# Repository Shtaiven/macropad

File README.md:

# QMK Macropad 5x5

A 5x5 key macropad with USB-C connector for Cherry MX-style switches.

## Repo structure

* [ecad](ecad) contains the electrical CAD files (KiCad).
* [mcad](mcad) contains the mechanical CAD files (SolidWorks).

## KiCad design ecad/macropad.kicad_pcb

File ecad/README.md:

# PCB Design

## MCU preferences

* Support both QMK (ChibiOS) and custom ducky firmware.
* MCU must be hand solderable.
* Must have USB stack  on SoC.
* ARM Cortex 32-bit based (M0 or M4).
* Ideally below $15.
* Support mounting as mass storage.
* Support DFU.
* UF2 support?

## Board preferences

* Shouldn't be too big, reduce from 25 keys. 4x4? 3x5?
* Differentiate from the ducky pad.
* Addressable LEDs.
* Optional rotary encoders.
* Hotswap.
* Numpad compatibility?

## MCUs considered

| MCU | Arch | Bit | Clock | Flash | RAM | I/O | QMK | USB | Note |
| --- | ---- | --- | ----- | ----- | --- | --- | --- | --- | ---- |
| [ATmega32u4](https://www.microchip.com/wwwproducts/en/ATmega32U4) | AVR | 8 | 16MHz | 32KB | 2.5KB | 26 | x | x | Arduino UNO and baseline for QMK |
| [STM32F042G6](https://www.st.com/content/st_com/en/products/microcontrollers-microprocessors/stm32-32-bit-arm-cortex-mcus/stm32-mainstream-mcus/stm32f0-series/stm32f0x2/stm32f042g6.html) | ARM Cortex-M0 | 32 | 48MHz | 32KB | 6KB | 38 | x | x | Used by duckyPad |
| [AT32UC3B1256](https://www.microchip.com/wwwproducts/en/AT32UC3B1256) | AVR | 32 | 60MHz | 64KB | 32KB | 28 |  | x | Used by USB Rubber Ducky |
| [STM32F303CCT6](https://www.st.com/en/microcontrollers-microprocessors/stm32f303cc.html) | ARM Cortex-M4 | 32 | 72MHz | 256KB | 40KB | 37 | x | x | Used by Proton C |
| __[STM32F103C6T6A](https://www.st.com/en/microcontrollers-microprocessors/stm32f103c6.html)__ | ARM Cortex-M3 | 32 | 72MHz | 32KB | 10KB | 37 | x | x | Pin compatible with STM32F303CCT6 |

## Specifications

| Parameter | Value |
| --------- | ----- |
| Board thickness | X mm |

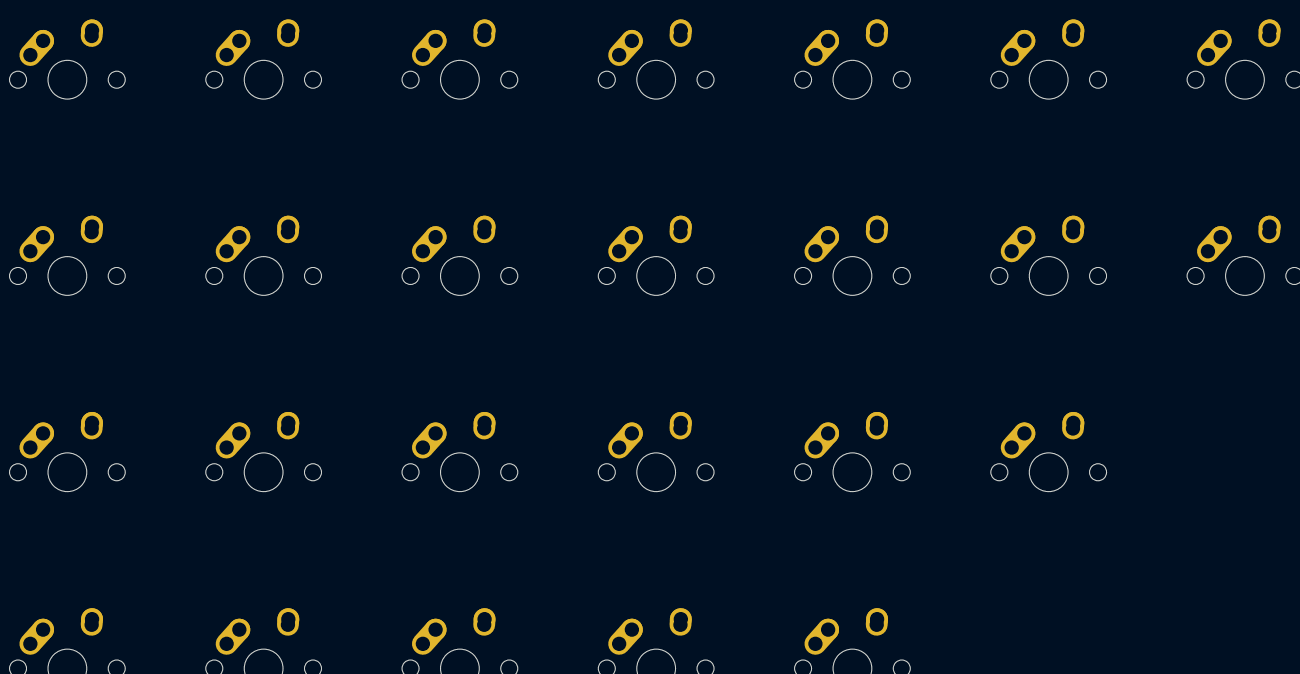
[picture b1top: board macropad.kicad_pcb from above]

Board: 2 copper layers, 25 parts (0 on the bottom side), 5 nets, no tracks yet.

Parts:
MX1, MX2, MX3, MX4, MX5, MX6, MX7, MX8, MX9, MX10, MX11, MX12, MX13, MX14, MX15, MX16, MX17, MX18, MX19, MX20, MX21, MX22, MX23, MX24, MX25: MX-NoLED; MX-1U-NoLED

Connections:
COL0: MX1.1, MX6.1, MX11.1, MX16.1, MX21.1
COL1: MX2.1, MX7.1, MX12.1, MX17.1, MX22.1
COL2: MX3.1, MX8.1, MX13.1, MX18.1, MX23.1
COL3: MX4.1, MX9.1, MX14.1, MX19.1, MX24.1
COL4: MX5.1, MX10.1, MX15.1, MX20.1, MX25.1

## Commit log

2021-03-24 Added README and gitignore
2021-03-24 Added blank READMEs to folders
2021-03-24 Add submodules
2021-03-24 Add license
2021-03-26 Add key matrix and update gitignore
2021-04-01 Write down some notes on MCU research and requirements
2021-04-05 Decided on and selected MCU
2021-04-11 Placed macropad into a box ins sch
